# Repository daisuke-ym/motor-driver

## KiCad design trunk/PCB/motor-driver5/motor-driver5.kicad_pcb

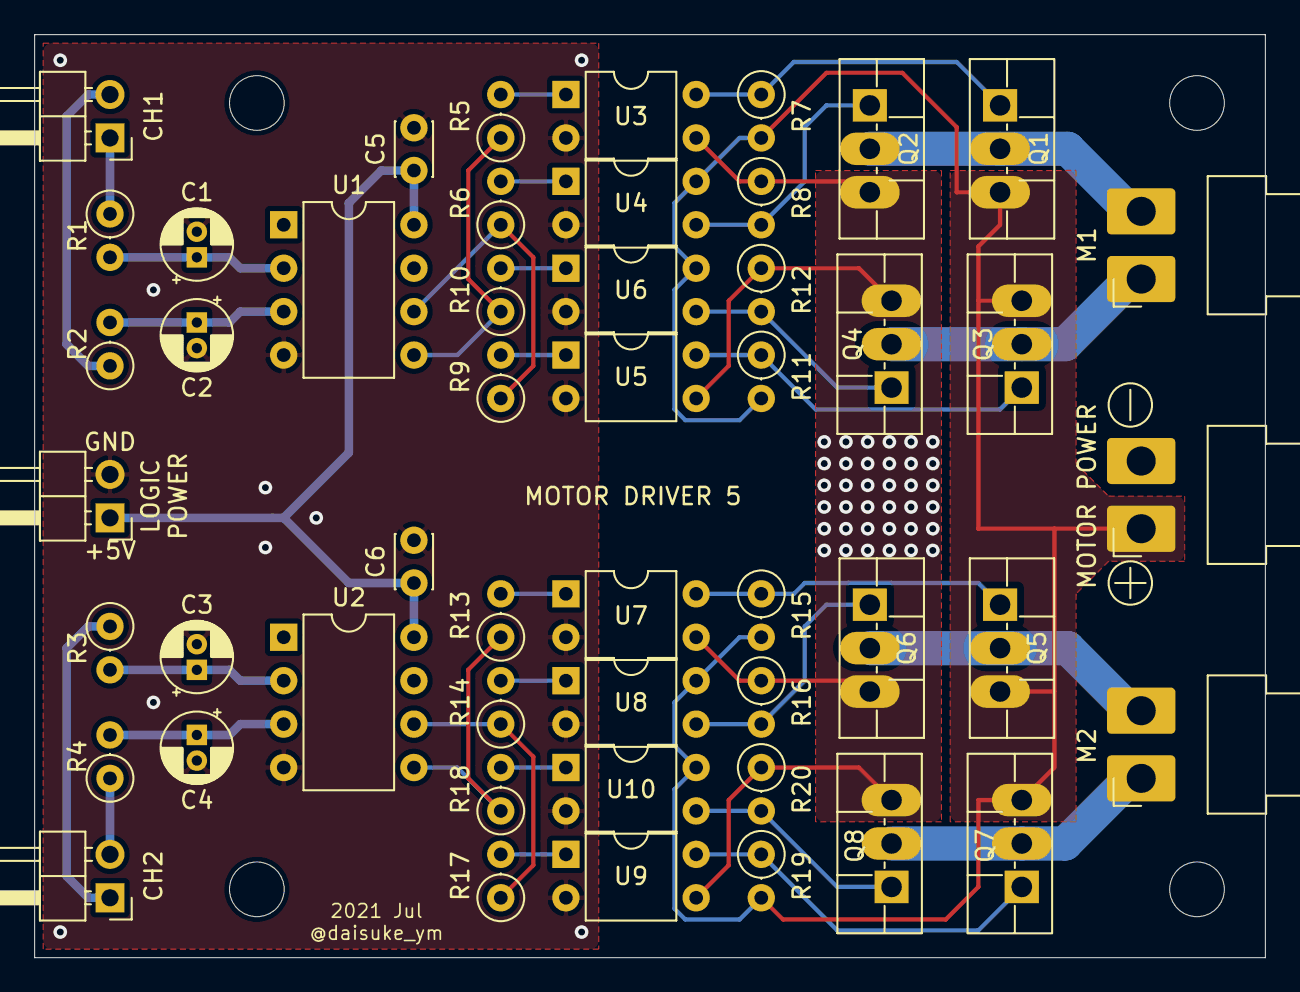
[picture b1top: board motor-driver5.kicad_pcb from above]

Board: 2 copper layers, 72.0 x 54.0 mm, 50 parts (0 on the bottom side), 36 nets.

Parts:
C1, C2, C3, C4: 10u; CP_Radial_D4.0mm_P1.50mm
C5, C6: 0.1u; C_Disc_D3.0mm_W2.0mm_P2.50mm
J1: Motor Power; JST_VH_B2PS-VH_1x02_P3.96mm_Horizontal
J2: Logic Power; PinHeader_1x02_P2.54mm_Horizontal
J3: Input Ch1; PinHeader_1x02_P2.54mm_Horizontal
J4: Input Ch2; PinHeader_1x02_P2.54mm_Horizontal
M1, M2: Motor_DC; JST_VH_B2PS-VH_1x02_P3.96mm_Horizontal
Q1, Q3, Q5, Q7: Q_PMOS_GDS; TO-220F-3_Vertical
Q2, Q4, Q6, Q8: Q_NMOS_GDS; TO-220F-3_Vertical
R1, R2, R3, R4: 4k7; R_Axial_DIN0207_L6.3mm_D2.5mm_P2.54mm_Vertical
R5, R6, R9, R10, R13, R14, R17, R18: 330; R_Axial_DIN0207_L6.3mm_D2.5mm_P2.54mm_Vertical
R7, R8, R11, R12, R15, R16, R19, R20: 2k2; R_Axial_DIN0207_L6.3mm_D2.5mm_P2.54mm_Vertical
U1, U2: ATtiny85-20PU; DIP-8_W7.62mm
U3, U4, U5, U6, U7, U8, U9, U10: TLP785; DIP-4_W7.62mm

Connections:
+5V: C5.1, C6.1, J2.1, U1.8, U2.8
+BATT: J1.1, Q1.3, Q3.3, Q5.3, Q7.3, R7.2, R11.2, R15.2, R19.2, U4.4, U6.4, U8.4, U10.4
/IN1A: J3.1, R1.1
/IN1AA: C1.1, R1.2, U1.2
/IN1B: J3.2, R2.1
/IN1BA: C2.1, R2.2, U1.3
/IN2A: J4.1, R3.1
/IN2AA: C3.1, R3.2, U2.2
/IN2B: J4.2, R4.1
/IN2BA: C4.1, R4.2, U2.3
/PC1A: R5.1, R10.1, U1.5
/PC1B: R6.1, R9.1, U1.6
/PC2A: R13.1, R18.1, U2.5
/PC2B: R14.1, R17.1, U2.6
GND: C1.2, C2.2, C3.2, C4.2, C5.2, C6.2, J2.2, U1.4, U2.4, U3.2, U4.2, U5.2, U6.2, U7.2, U8.2, U9.2, U10.2
GNDPWR: J1.2, Q2.3, Q4.3, Q6.3, Q8.3, R8.1, R12.1, R16.1, R20.1, U3.3, U5.3, U7.3, U9.3
unnamed: M1.1, Q3.2, Q4.2
unnamed: M1.2, Q1.2, Q2.2
unnamed: M2.1, Q7.2, Q8.2
unnamed: M2.2, Q5.2, Q6.2
unnamed: Q1.1, R7.1, U3.4
unnamed: Q2.1, R8.2, U4.3
unnamed: Q3.1, R11.1, U5.4
unnamed: Q4.1, R12.2, U6.3
unnamed: Q5.1, R15.1, U7.4
unnamed: Q6.1, R16.2, U8.3
unnamed: Q7.1, R19.1, U9.4
unnamed: Q8.1, R20.2, U10.3
unnamed: R5.2, U3.1
unnamed: R6.2, U4.1
unnamed: R9.2, U5.1
unnamed: R10.2, U6.1
unnamed: R13.2, U7.1
unnamed: R14.2, U8.1
unnamed: R17.2, U9.1
unnamed: R18.2, U10.1

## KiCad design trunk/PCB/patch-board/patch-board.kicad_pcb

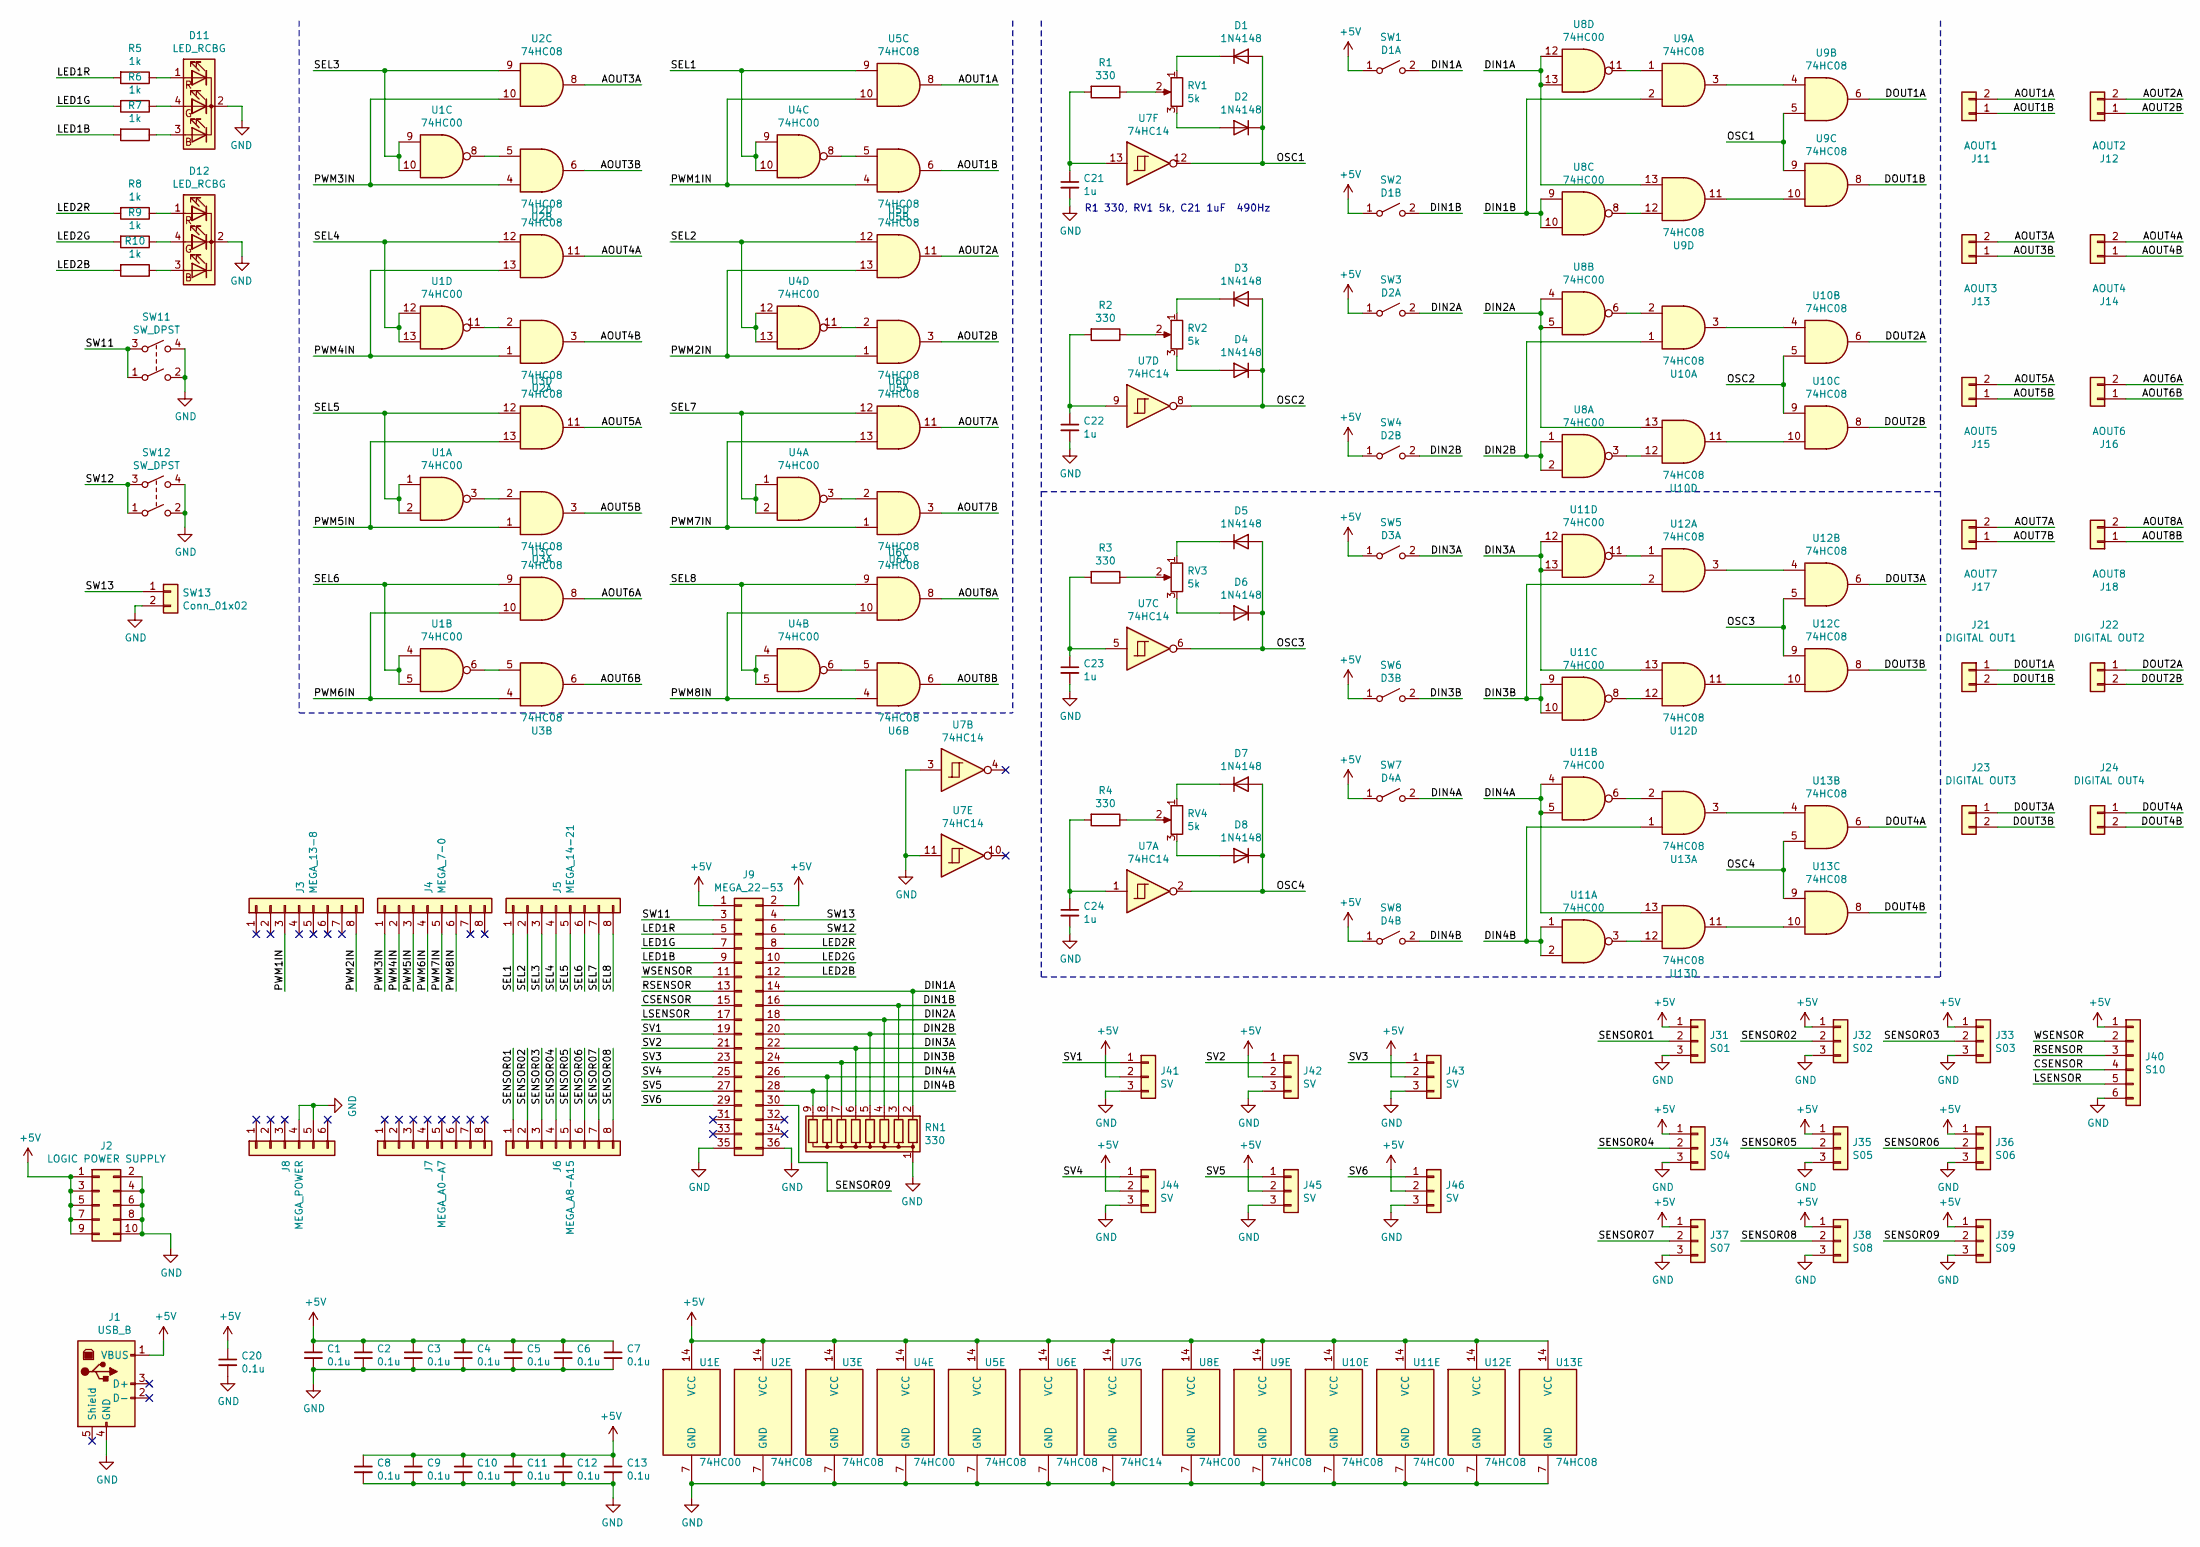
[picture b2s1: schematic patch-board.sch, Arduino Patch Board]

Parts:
C1, C2, C3, C4, C5, C6, C7, C8, C9, C10, C11, C12, C13, C20: 0.1u; C_Disc_D3.4mm_W2.1mm_P2.50mm
C21, C22, C23, C24: 1u; C_Disc_D3.4mm_W2.1mm_P2.50mm
D1, D2, D3, D4, D5, D6, D7, D8: 1N4148; D_DO-35_SOD27_P7.62mm_Horizontal
D11, D12: LED_RCBG; LED_D5.0mm-4_RGB
J1: USB_B; USB_B_OST_USB-B1HSxx_Horizontal
J2: LOGIC POWER SUPPLY; PinHeader_2x05_P2.54mm_Vertical
J3: MEGA_13-8; PinHeader_1x08_P2.54mm_Vertical
J4: MEGA_7-0; PinHeader_1x08_P2.54mm_Vertical
J5: MEGA_14-21; PinHeader_1x08_P2.54mm_Vertical
J6: MEGA_A8-A15; PinHeader_1x08_P2.54mm_Vertical
J7: MEGA_A0-A7; PinHeader_1x08_P2.54mm_Vertical
J8: MEGA_POWER; PinHeader_1x06_P2.54mm_Vertical
J9: MEGA_22-53; PinHeader_2x18_P2.54mm_Vertical
J11: AOUT1; PinHeader_1x02_P2.54mm_Vertical
J12: AOUT2; PinHeader_1x02_P2.54mm_Vertical
J13: AOUT3; PinHeader_1x02_P2.54mm_Vertical
J14: AOUT4; PinHeader_1x02_P2.54mm_Vertical
J15: AOUT5; PinHeader_1x02_P2.54mm_Vertical
J16: AOUT6; PinHeader_1x02_P2.54mm_Vertical
J17: AOUT7; PinHeader_1x02_P2.54mm_Vertical
J18: AOUT8; PinHeader_1x02_P2.54mm_Vertical
J21: DIGITAL OUT1; PinHeader_1x02_P2.54mm_Vertical
J22: DIGITAL OUT2; PinHeader_1x02_P2.54mm_Vertical
J23: DIGITAL OUT3; PinHeader_1x02_P2.54mm_Vertical
J24: DIGITAL OUT4; PinHeader_1x02_P2.54mm_Vertical
J31: S01; PinHeader_1x03_P2.54mm_Vertical
J32: S02; PinHeader_1x03_P2.54mm_Vertical
J33: S03; PinHeader_1x03_P2.54mm_Vertical
J34: S04; PinHeader_1x03_P2.54mm_Vertical
J35: S05; PinHeader_1x03_P2.54mm_Vertical
J36: S06; PinHeader_1x03_P2.54mm_Vertical
J37: S07; PinHeader_1x03_P2.54mm_Vertical
J38: S08; PinHeader_1x03_P2.54mm_Vertical
J39: S09; PinHeader_1x03_P2.54mm_Vertical
J40: S10; PinHeader_1x06_P2.54mm_Vertical
J41, J42, J43, J44, J45, J46: SV; PinHeader_1x03_P2.54mm_Vertical
R1, R2, R3, R4: 330; R_Axial_DIN0207_L6.3mm_D2.5mm_P10.16mm_Horizontal
R5, R6, R7, R8, R9, R10: 1k; R_Axial_DIN0207_L6.3mm_D2.5mm_P10.16mm_Horizontal
RN1: 330; R_Array_SIP9
RV1, RV2, RV3, RV4: 5k; GF063P1
SW1: D1A; TactSW_TVBP06_3.5x6.0-ThroughHole
SW2: D1B; TactSW_TVBP06_3.5x6.0-ThroughHole
SW3: D2A; TactSW_TVBP06_3.5x6.0-ThroughHole
SW4: D2B; TactSW_TVBP06_3.5x6.0-ThroughHole
SW5: D3A; TactSW_TVBP06_3.5x6.0-ThroughHole
SW6: D3B; TactSW_TVBP06_3.5x6.0-ThroughHole
SW7: D4A; TactSW_TVBP06_3.5x6.0-ThroughHole
SW8: D4B; TactSW_TVBP06_3.5x6.0-ThroughHole
SW11, SW12: SW_DPST; DTS-6-V-2
SW13: Conn_01x02; PinHeader_1x02_P2.54mm_Vertical
U1, U4, U8, U11: 74HC00; SO-14_5.3x10.2mm_P1.27mm
U2, U3, U5, U6, U9, U10, U12, U13: 74HC08; SO-14_5.3x10.2mm_P1.27mm
U7: 74HC14; SO-14_5.3x10.2mm_P1.27mm

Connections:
+5V: C1.1, C2.1, C3.1, C4.1, C5.1, C6.1, C7.1, C8.1, C9.1, C10.1, C11.1, C12.1, C13.1, C20.1, J1.1 (VBUS), J2.1, J2.3, J2.5, J2.7, J2.9, J9.1, J9.2, J31.1, J32.1, J33.1, J34.1, J35.1, J36.1, J37.1, J38.1, J39.1, J40.1, J41.2, J42.2, J43.2, J44.2, J45.2, J46.2, SW1.1 (A), SW2.1 (A), SW3.1 (A), SW4.1 (A), SW5.1 (A), SW6.1 (A), SW7.1 (A), SW8.1 (A), U1.14 (VCC), U2.14 (VCC), U3.14 (VCC), U4.14 (VCC), U5.14 (VCC), U6.14 (VCC), U7.14 (VCC), U8.14 (VCC), U9.14 (VCC), U10.14 (VCC), U11.14 (VCC), U12.14 (VCC), U13.14 (VCC)
/AOUT1A: J11.2, U5.8
/AOUT1B: J11.1, U5.6
/AOUT2A: J12.2, U5.11
/AOUT2B: J12.1, U5.3
/AOUT3A: J13.2, U2.8
/AOUT3B: J13.1, U2.6
/AOUT4A: J14.2, U2.11
/AOUT4B: J14.1, U2.3
/AOUT5A: J15.2, U3.11
/AOUT5B: J15.1, U3.3
/AOUT6A: J16.2, U3.8
/AOUT6B: J16.1, U3.6
/AOUT7A: J17.2, U6.11
/AOUT7B: J17.1, U6.3
/AOUT8A: J18.2, U6.8
/AOUT8B: J18.1, U6.6
/CSENSOR: J9.15, J40.4
/DIN1A: J9.14, RN1.2 (R1), SW1.2 (B), U8.12, U8.13, U9.13
/DIN1B: J9.16, RN1.3 (R2), SW2.2 (B), U8.9, U8.10, U9.2
/DIN2A: J9.18, RN1.4 (R3), SW3.2 (B), U8.4, U8.5, U10.13
/DIN2B: J9.20, RN1.5 (R4), SW4.2 (B), U8.1, U8.2, U10.1
/DIN3A: J9.22, RN1.6 (R5), SW5.2 (B), U11.12, U11.13, U12.13
/DIN3B: J9.24, RN1.7 (R6), SW6.2 (B), U11.9, U11.10, U12.2
/DIN4A: J9.26, RN1.8 (R7), SW7.2 (B), U11.4, U11.5, U13.13
/DIN4B: J9.28, RN1.9 (R8), SW8.2 (B), U11.1, U11.2, U13.1
/DOUT1A: J21.1, U9.6
/DOUT1B: J21.2, U9.8
/DOUT2A: J22.1, U10.6
/DOUT2B: J22.2, U10.8
/DOUT3A: J23.1, U12.6
/DOUT3B: J23.2, U12.8
/DOUT4A: J24.1, U13.6
/DOUT4B: J24.2, U13.8
/LED1B: J9.9, R7.2
/LED1G: J9.7, R6.2
/LED1R: J9.5, R5.2
/LED2B: J9.12, R10.2
/LED2G: J9.10, R9.2
/LED2R: J9.8, R8.2
/LSENSOR: J9.17, J40.5
/OSC1: D1.2 (A), D2.1 (K), U7.12, U9.5, U9.9
/OSC2: D3.2 (A), D4.1 (K), U7.8, U10.5, U10.9
/OSC3: D5.2 (A), D6.1 (K), U7.6, U12.5, U12.9
/OSC4: D7.2 (A), D8.1 (K), U7.2, U13.5, U13.9
/PWM1IN: J3.3, U5.4, U5.10
/PWM2IN: J3.8, U5.1, U5.13
/PWM3IN: J4.1, U2.4, U2.10
/PWM4IN: J4.2, U2.1, U2.13
/PWM5IN: J4.3, U3.1, U3.13
/PWM6IN: J4.4, U3.4, U3.10
/PWM7IN: J4.5, U6.1, U6.13
/PWM8IN: J4.6, U6.4, U6.10
/RSENSOR: J9.13, J40.3
/SEL1: J5.1, U4.9, U4.10, U5.9
/SEL2: J5.2, U4.12, U4.13, U5.12
/SEL3: J5.3, U1.9, U1.10, U2.9
/SEL4: J5.4, U1.12, U1.13, U2.12
/SEL5: J5.5, U1.1, U1.2, U3.12
/SEL6: J5.6, U1.4, U1.5, U3.9
/SEL7: J5.7, U4.1, U4.2, U6.12
/SEL8: J5.8, U4.4, U4.5, U6.9
/SENSOR01: J6.1, J31.2
/SENSOR02: J6.2, J32.2
/SENSOR03: J6.3, J33.2
/SENSOR04: J6.4, J34.2
/SENSOR05: J6.5, J35.2
/SENSOR06: J6.6, J36.2
/SENSOR07: J6.7, J37.2
/SENSOR08: J6.8, J38.2
/SENSOR09: J9.30, J39.2
/SV1: J9.19, J41.1
/SV2: J9.21, J42.1
/SV3: J9.23, J43.1
/SV4: J9.25, J44.1
/SV5: J9.27, J45.1
/SV6: J9.29, J46.1
/SW11: J9.3, SW11.1, SW11.3
/SW12: J9.6, SW12.1, SW12.3
/SW13: J9.4, SW13.1
/WSENSOR: J9.11, J40.2
GND: C1.2, C2.2, C3.2, C4.2, C5.2, C6.2, C7.2, C8.2, C9.2, C10.2, C11.2, C12.2, C13.2, C20.2, C21.2, C22.2, C23.2, C24.2, D11.2 (K), D12.2 (K), J1.4 (GND), J2.2, J2.4, J2.6, J2.8, J2.10, J8.4, J8.5, J9.35, J9.36, J31.3, J32.3, J33.3, J34.3, J35.3, J36.3, J37.3, J38.3, J39.3, J40.6, J41.3, J42.3, J43.3, J44.3, J45.3, J46.3, RN1.1 (common), SW11.2, SW11.4, SW12.2, SW12.4, SW13.2, U1.7 (GND), U2.7 (GND), U3.7 (GND), U4.7 (GND), U5.7 (GND), U6.7 (GND), U7.3, U7.7 (GND), U7.11, U8.7 (GND), U9.7 (GND), U10.7 (GND), U11.7 (GND), U12.7 (GND), U13.7 (GND)
unnamed: C21.1, R1.2, U7.13
unnamed: C22.1, R2.2, U7.9
unnamed: C23.1, R3.2, U7.5
unnamed: C24.1, R4.2, U7.1
unnamed: D1.1 (K), RV1.1
unnamed: D2.2 (A), RV1.3
unnamed: D3.1 (K), RV2.1
unnamed: D4.2 (A), RV2.3
unnamed: D5.1 (K), RV3.1
unnamed: D6.2 (A), RV3.3
unnamed: D7.1 (K), RV4.1
unnamed: D8.2 (A), RV4.3
unnamed: D11.1 (RA), R5.1
unnamed: D11.3 (BA), R7.1
unnamed: D11.4 (GA), R6.1
unnamed: D12.1 (RA), R8.1
unnamed: D12.3 (BA), R10.1
unnamed: D12.4 (GA), R9.1
unnamed: R1.1, RV1.2
unnamed: R2.1, RV2.2
unnamed: R3.1, RV3.2
unnamed: R4.1, RV4.2
unnamed: U1.3, U3.2
unnamed: U1.6, U3.5
unnamed: U1.8, U2.5
unnamed: U1.11, U2.2
unnamed: U4.3, U6.2
unnamed: U4.6, U6.5
unnamed: U4.8, U5.5
unnamed: U4.11, U5.2
unnamed: U8.8, U9.12
unnamed: U8.11, U9.1
unnamed: U9.3, U9.4
unnamed: U9.10, U9.11
unnamed: U8.6, U10.2
unnamed: U10.3, U10.4
unnamed: U10.10, U10.11
unnamed: U8.3, U10.12
unnamed: U11.3, U13.12
unnamed: U11.6, U13.2
unnamed: U11.8, U12.12
unnamed: U11.11, U12.1
unnamed: U12.3, U12.4
unnamed: U12.10, U12.11
unnamed: U13.3, U13.4
unnamed: U13.10, U13.11

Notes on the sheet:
R1 330, RV1 5k, C21 1uF 490Hz

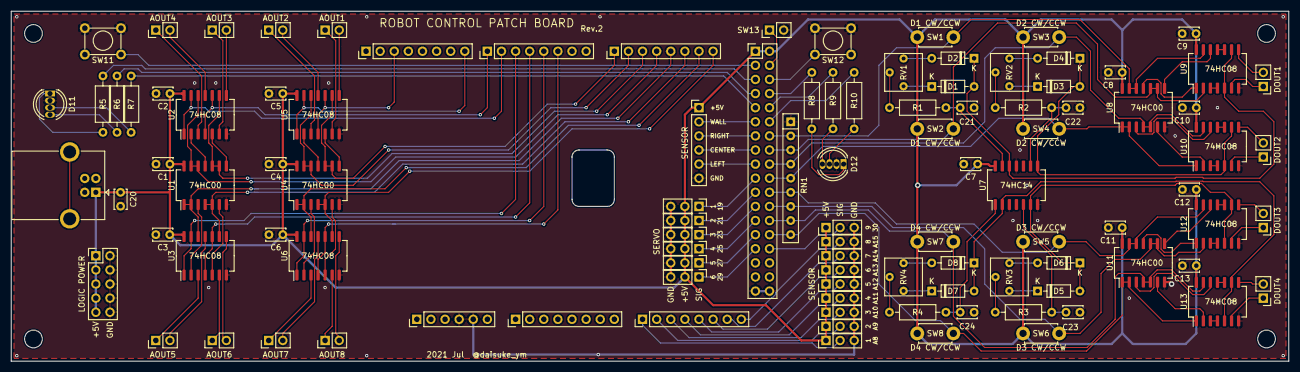
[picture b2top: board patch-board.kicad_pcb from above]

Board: 2 copper layers, 230.0 x 63.0 mm, 104 parts (0 on the bottom side), 128 nets.

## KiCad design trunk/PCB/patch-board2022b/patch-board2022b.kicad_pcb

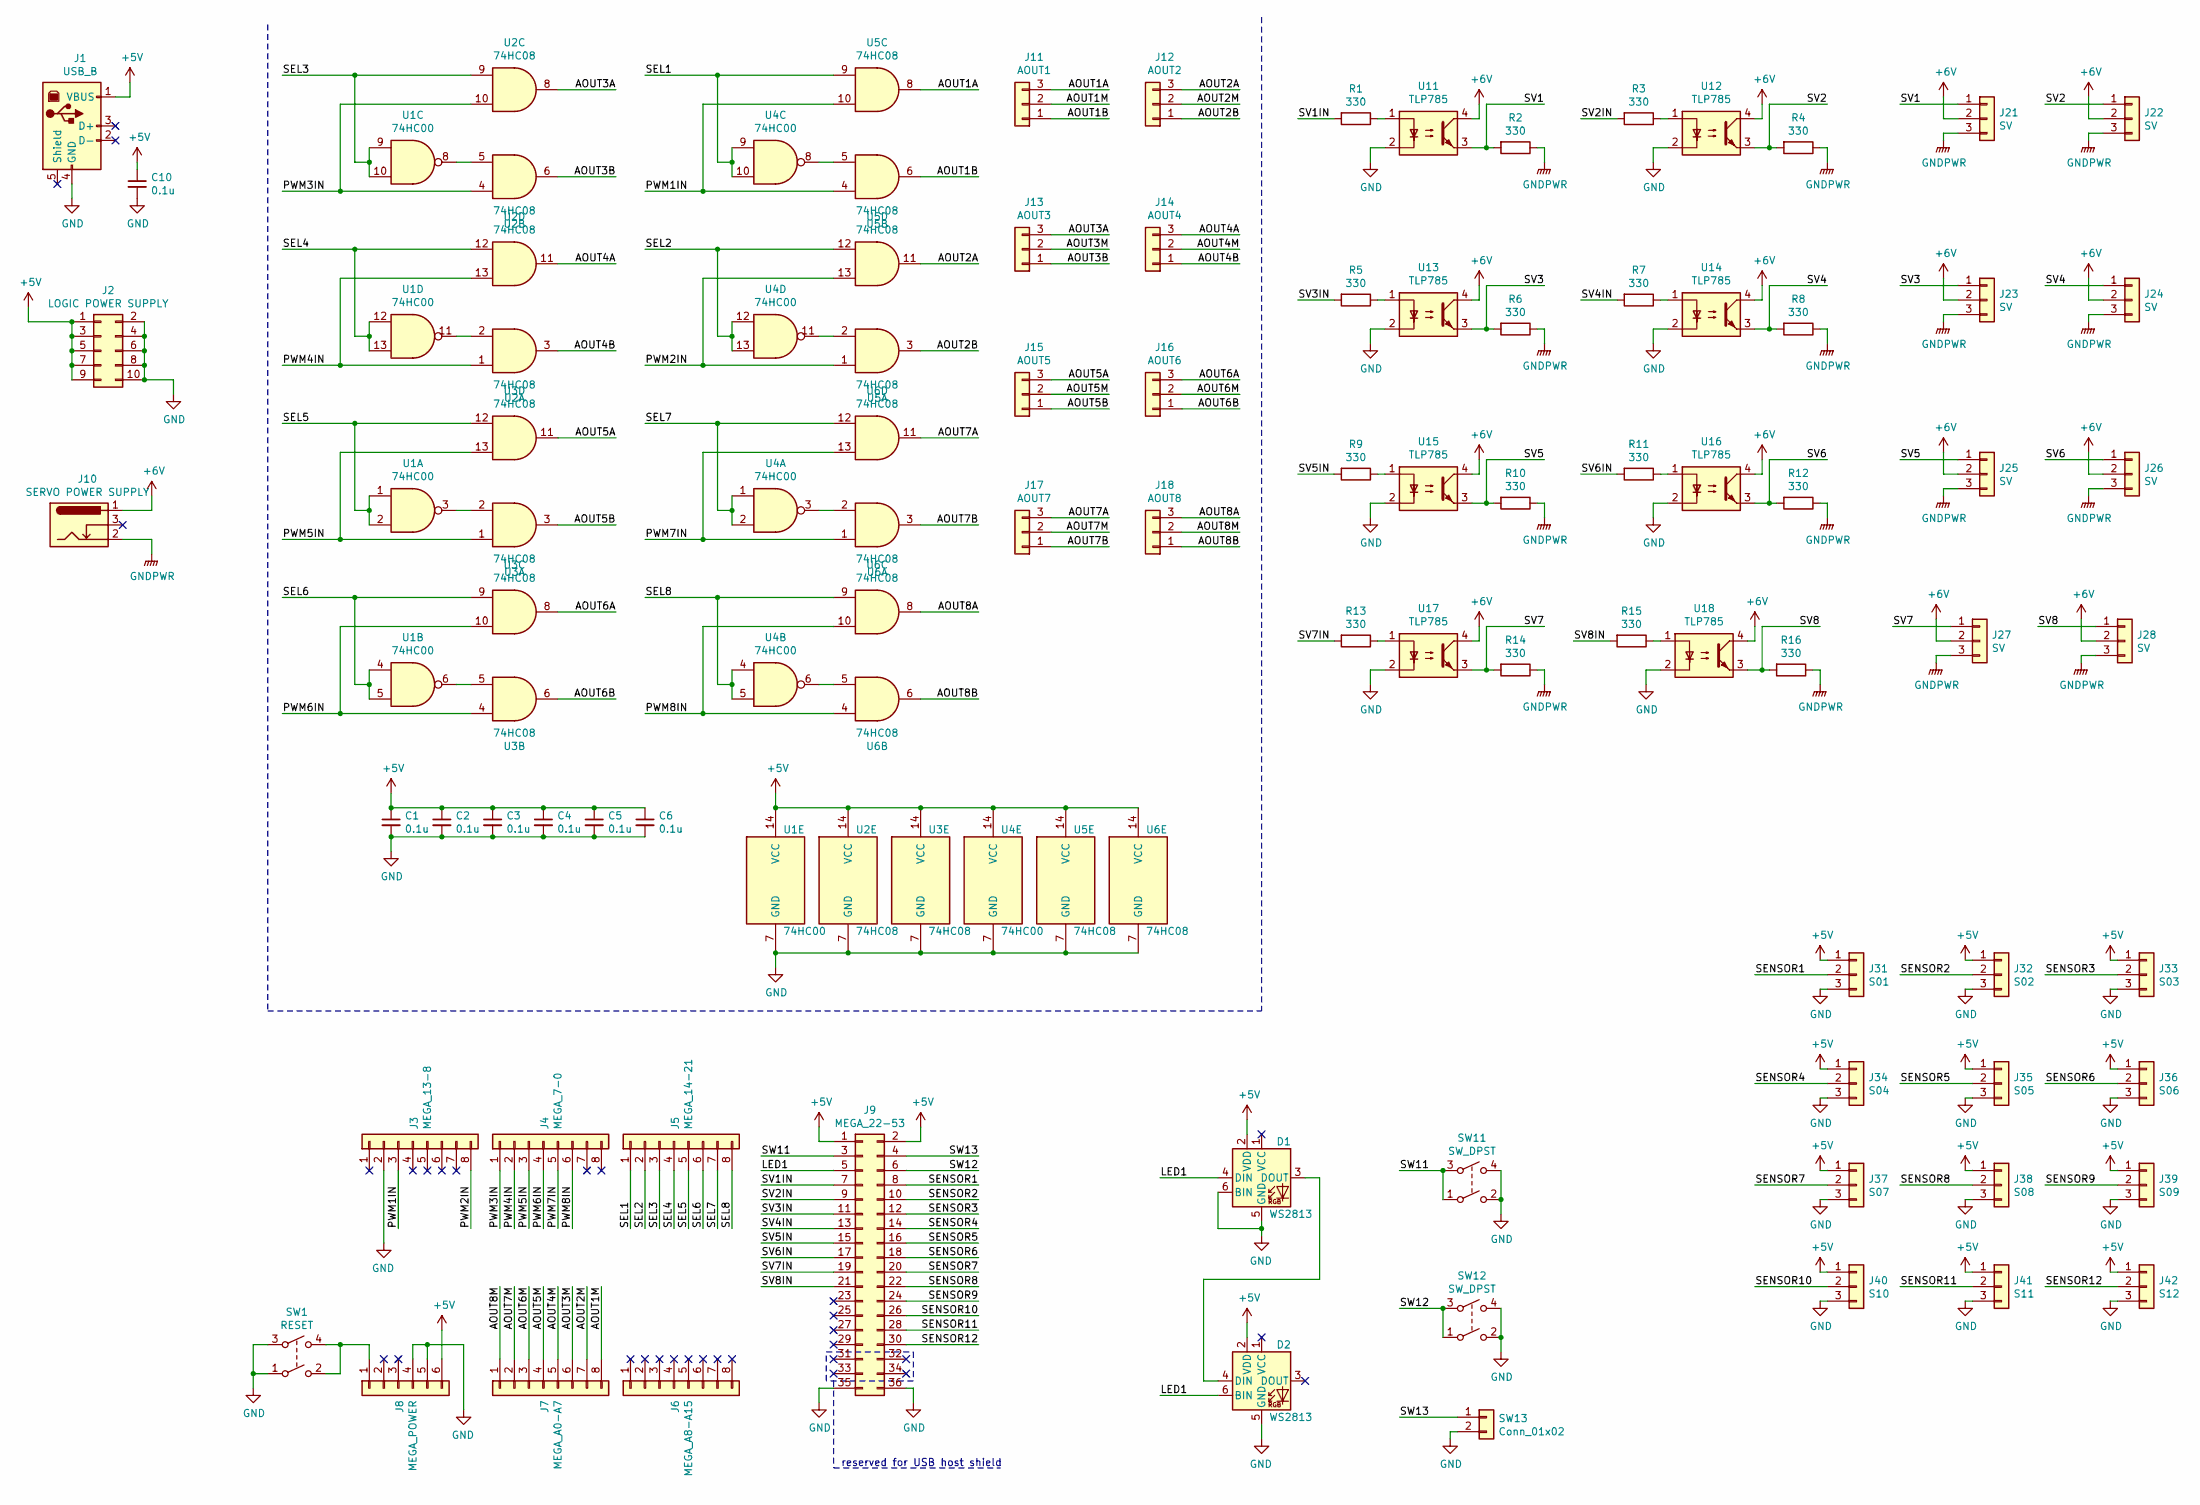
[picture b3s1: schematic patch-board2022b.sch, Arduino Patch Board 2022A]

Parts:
C1, C2, C3, C4, C5, C6, C10: 0.1u; C_Disc_D3.4mm_W2.1mm_P2.50mm
D1, D2: WS2813; LED_WS2812_PLCC6_5.0x5.0mm_P1.6mm
J1: USB_B; USB_B_OST_USB-B1HSxx_Horizontal
J2: LOGIC POWER SUPPLY; PinHeader_2x05_P2.54mm_Vertical
J3: MEGA_13-8; PinHeader_1x08_P2.54mm_Vertical
J4: MEGA_7-0; PinHeader_1x08_P2.54mm_Vertical
J5: MEGA_14-21; PinHeader_1x08_P2.54mm_Vertical
J6: MEGA_A8-A15; PinHeader_1x08_P2.54mm_Vertical
J7: MEGA_A0-A7; PinHeader_1x08_P2.54mm_Vertical
J8: MEGA_POWER; PinHeader_1x06_P2.54mm_Vertical
J9: MEGA_22-53; PinHeader_2x18_P2.54mm_Vertical
J10: SERVO POWER SUPPLY; BarrelJack_Horizontal
J11: AOUT1; PinHeader_1x03_P2.54mm_Vertical
J12: AOUT2; PinHeader_1x03_P2.54mm_Vertical
J13: AOUT3; PinHeader_1x03_P2.54mm_Vertical
J14: AOUT4; PinHeader_1x03_P2.54mm_Vertical
J15: AOUT5; PinHeader_1x03_P2.54mm_Vertical
J16: AOUT6; PinHeader_1x03_P2.54mm_Vertical
J17: AOUT7; PinHeader_1x03_P2.54mm_Vertical
J18: AOUT8; PinHeader_1x03_P2.54mm_Vertical
J21, J22, J23, J24, J25, J26, J27, J28: SV; PinHeader_1x03_P2.54mm_Vertical
J31: S01; PinHeader_1x03_P2.54mm_Vertical
J32: S02; PinHeader_1x03_P2.54mm_Vertical
J33: S03; PinHeader_1x03_P2.54mm_Vertical
J34: S04; PinHeader_1x03_P2.54mm_Vertical
J35: S05; PinHeader_1x03_P2.54mm_Vertical
J36: S06; PinHeader_1x03_P2.54mm_Vertical
J37: S07; PinHeader_1x03_P2.54mm_Vertical
J38: S08; PinHeader_1x03_P2.54mm_Vertical
J39: S09; PinHeader_1x03_P2.54mm_Vertical
J40: S10; PinHeader_1x03_P2.54mm_Vertical
J41: S11; PinHeader_1x03_P2.54mm_Vertical
J42: S12; PinHeader_1x03_P2.54mm_Vertical
R1, R2, R3, R4, R5, R6, R7, R8, R9, R10, R11, R12, R13, R14, R15, R16: 330; R_Axial_DIN0207_L6.3mm_D2.5mm_P10.16mm_Horizontal
SW1: RESET; DTS-6-V-2
SW11, SW12: SW_DPST; DTS-6-V-2
SW13: Conn_01x02; PinHeader_1x02_P2.54mm_Vertical
U1, U4: 74HC00; SO-14_5.3x10.2mm_P1.27mm
U2, U3, U5, U6: 74HC08; SO-14_5.3x10.2mm_P1.27mm
U11, U12, U13, U14, U15, U16, U17, U18: TLP785; DIP-4_W7.62mm

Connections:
+5V: C1.1, C2.1, C3.1, C4.1, C5.1, C6.1, C10.1, D1.2 (VDD), D2.2 (VDD), J1.1 (VBUS), J2.1, J2.3, J2.5, J2.7, J2.9, J8.6, J9.1, J9.2, J31.1, J32.1, J33.1, J34.1, J35.1, J36.1, J37.1, J38.1, J39.1, J40.1, J41.1, J42.1, U1.14 (VCC), U2.14 (VCC), U3.14 (VCC), U4.14 (VCC), U5.14 (VCC), U6.14 (VCC)
+6V: J10.1, J21.2, J22.2, J23.2, J24.2, J25.2, J26.2, J27.2, J28.2, U11.4, U12.4, U13.4, U14.4, U15.4, U16.4, U17.4, U18.4
/AOUT1A: J11.3, U5.8
/AOUT1B: J11.1, U5.6
/AOUT1M: J7.8, J11.2
/AOUT2A: J12.3, U5.11
/AOUT2B: J12.1, U5.3
/AOUT2M: J7.7, J12.2
/AOUT3A: J13.3, U2.8
/AOUT3B: J13.1, U2.6
/AOUT3M: J7.6, J13.2
/AOUT4A: J14.3, U2.11
/AOUT4B: J14.1, U2.3
/AOUT4M: J7.5, J14.2
/AOUT5A: J15.3, U3.11
/AOUT5B: J15.1, U3.3
/AOUT5M: J7.4, J15.2
/AOUT6A: J16.3, U3.8
/AOUT6B: J16.1, U3.6
/AOUT6M: J7.3, J16.2
/AOUT7A: J17.3, U6.11
/AOUT7B: J17.1, U6.3
/AOUT7M: J7.2, J17.2
/AOUT8A: J18.3, U6.8
/AOUT8B: J18.1, U6.6
/AOUT8M: J7.1, J18.2
/LED1: D1.4 (DIN), D2.6 (BIN), J9.5
/PWM1IN: J3.3, U5.4, U5.10
/PWM2IN: J3.8, U5.1, U5.13
/PWM3IN: J4.1, U2.4, U2.10
/PWM4IN: J4.2, U2.1, U2.13
/PWM5IN: J4.3, U3.1, U3.13
/PWM6IN: J4.4, U3.4, U3.10
/PWM7IN: J4.5, U6.1, U6.13
/PWM8IN: J4.6, U6.4, U6.10
/SEL1: J5.1, U4.9, U4.10, U5.9
/SEL2: J5.2, U4.12, U4.13, U5.12
/SEL3: J5.3, U1.9, U1.10, U2.9
/SEL4: J5.4, U1.12, U1.13, U2.12
/SEL5: J5.5, U1.1, U1.2, U3.12
/SEL6: J5.6, U1.4, U1.5, U3.9
/SEL7: J5.7, U4.1, U4.2, U6.12
/SEL8: J5.8, U4.4, U4.5, U6.9
/SENSOR1: J9.8, J31.2
/SENSOR2: J9.10, J32.2
/SENSOR3: J9.12, J33.2
/SENSOR4: J9.14, J34.2
/SENSOR5: J9.16, J35.2
/SENSOR6: J9.18, J36.2
/SENSOR7: J9.20, J37.2
/SENSOR8: J9.22, J38.2
/SENSOR9: J9.24, J39.2
/SENSOR10: J9.26, J40.2
/SENSOR11: J9.28, J41.2
/SENSOR12: J9.30, J42.2
/SV1: J21.1, R2.2, U11.3
/SV1IN: J9.7, R1.2
/SV2: J22.1, R4.2, U12.3
/SV2IN: J9.9, R3.2
/SV3: J23.1, R6.2, U13.3
/SV3IN: J9.11, R5.2
/SV4: J24.1, R8.2, U14.3
/SV4IN: J9.13, R7.2
/SV5: J25.1, R10.2, U15.3
/SV5IN: J9.15, R9.2
/SV6: J26.1, R12.2, U16.3
/SV6IN: J9.17, R11.2
/SV7: J27.1, R14.2, U17.3
/SV7IN: J9.19, R13.2
/SV8: J28.1, R16.2, U18.3
/SV8IN: J9.21, R15.2
/SW11: J9.3, SW11.1, SW11.3
/SW12: J9.6, SW12.1, SW12.3
/SW13: J9.4, SW13.1
GND: C1.2, C2.2, C3.2, C4.2, C5.2, C6.2, C10.2, D1.5 (GND), D1.6 (BIN), D2.5 (GND), J1.4 (GND), J2.2, J2.4, J2.6, J2.8, J2.10, J3.2, J8.4, J8.5, J9.35, J9.36, J31.3, J32.3, J33.3, J34.3, J35.3, J36.3, J37.3, J38.3, J39.3, J40.3, J41.3, J42.3, SW1.1, SW1.3, SW11.2, SW11.4, SW12.2, SW12.4, SW13.2, U1.7 (GND), U2.7 (GND), U3.7 (GND), U4.7 (GND), U5.7 (GND), U6.7 (GND), U11.2, U12.2, U13.2, U14.2, U15.2, U16.2, U17.2, U18.2
GNDPWR: J10.2, J21.3, J22.3, J23.3, J24.3, J25.3, J26.3, J27.3, J28.3, R2.1, R4.1, R6.1, R8.1, R10.1, R12.1, R14.1, R16.1
unnamed: D1.3 (DOUT), D2.4 (DIN)
unnamed: J8.1, SW1.2, SW1.4
unnamed: R1.1, U11.1
unnamed: R3.1, U12.1
unnamed: R5.1, U13.1
unnamed: R7.1, U14.1
unnamed: R9.1, U15.1
unnamed: R11.1, U16.1
unnamed: R13.1, U17.1
unnamed: R15.1, U18.1
unnamed: U1.3, U3.2
unnamed: U1.6, U3.5
unnamed: U1.8, U2.5
unnamed: U1.11, U2.2
unnamed: U4.3, U6.2
unnamed: U4.6, U6.5
unnamed: U4.8, U5.5
unnamed: U4.11, U5.2

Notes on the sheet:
reserved for USB host shield

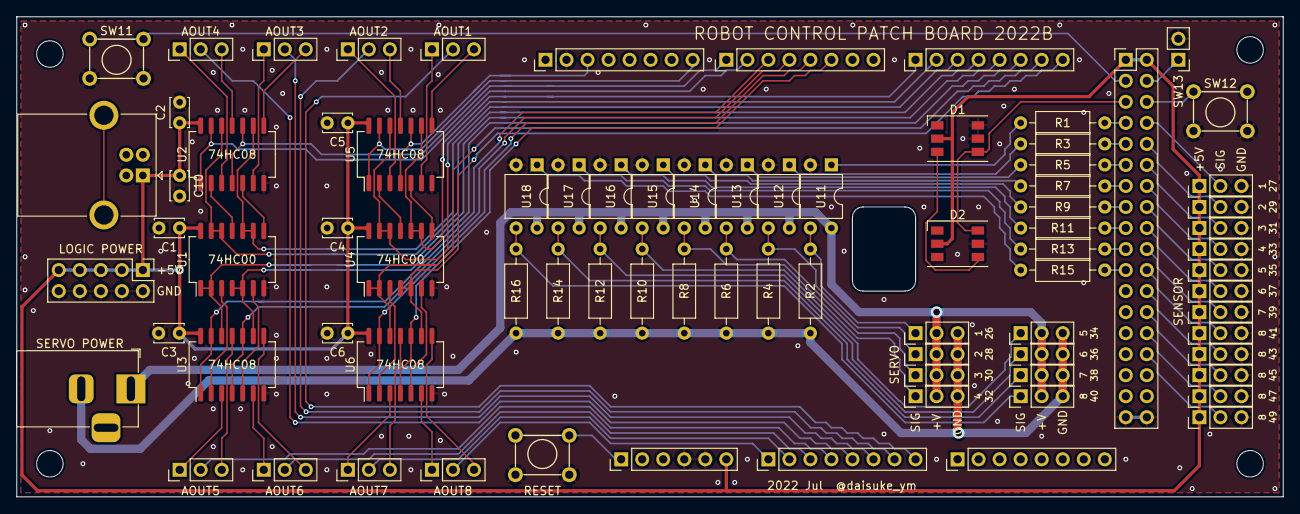
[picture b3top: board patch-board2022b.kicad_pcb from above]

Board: 2 copper layers, 153.0 x 58.0 mm, 81 parts (0 on the bottom side), 94 nets.

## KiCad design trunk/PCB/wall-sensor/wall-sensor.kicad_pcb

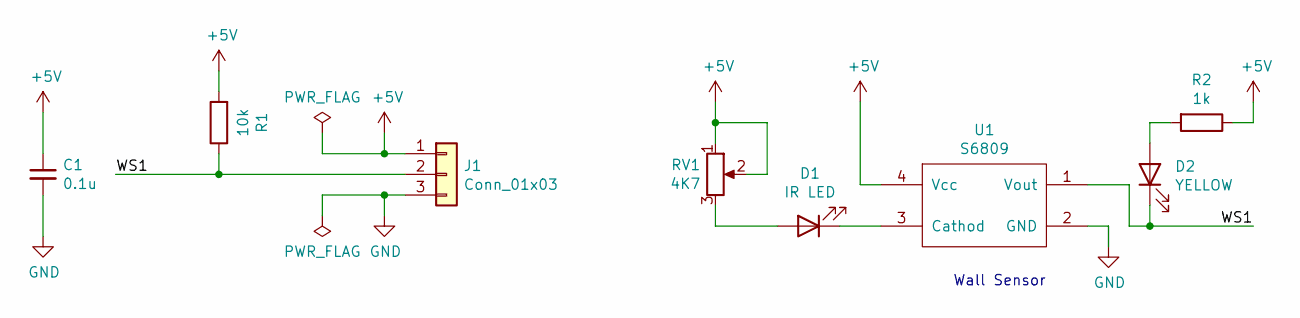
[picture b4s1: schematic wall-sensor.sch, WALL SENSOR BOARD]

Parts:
C1: 0.1u; C_Disc_D3.4mm_W2.1mm_P2.50mm
D1: IR LED; LED_D3.0mm_Horizontal_O3.81mm_Z6.0mm
D2: YELLOW; LED_D3.0mm_Clear
J1: Conn_01x03; PinHeader_1x03_P2.54mm_Horizontal
R1: 10k; R_Axial_DIN0207_L6.3mm_D2.5mm_P10.16mm_Horizontal
R2: 1k; R_Axial_DIN0207_L6.3mm_D2.5mm_P10.16mm_Horizontal
RV1: 4K7; GF063P1
U1: S6809; S6809_Horizontal_Facedown

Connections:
+5V: C1.1, J1.1, R1.2, R2.1, RV1.1, RV1.2, U1.4 (Vcc)
/WS1: D2.1 (K), J1.2, R1.1, U1.1 (Vout)
GND: C1.2, J1.3, U1.2 (GND)
unnamed: D1.1 (K), U1.3 (Cathod)
unnamed: D1.2 (A), RV1.3
unnamed: D2.2 (A), R2.2

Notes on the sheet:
Wall Sensor

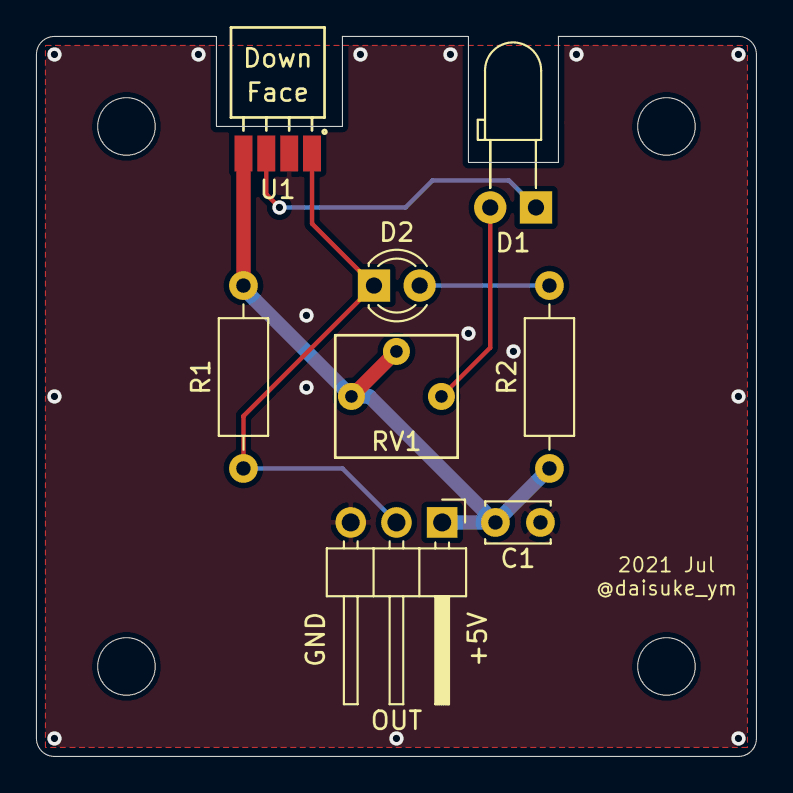
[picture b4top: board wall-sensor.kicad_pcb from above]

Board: 2 copper layers, 40.0 x 40.0 mm, 12 parts (0 on the bottom side), 6 nets.

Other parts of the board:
MH1, MH2, MH3, MH6: MountingHole_3.2mm_M3
